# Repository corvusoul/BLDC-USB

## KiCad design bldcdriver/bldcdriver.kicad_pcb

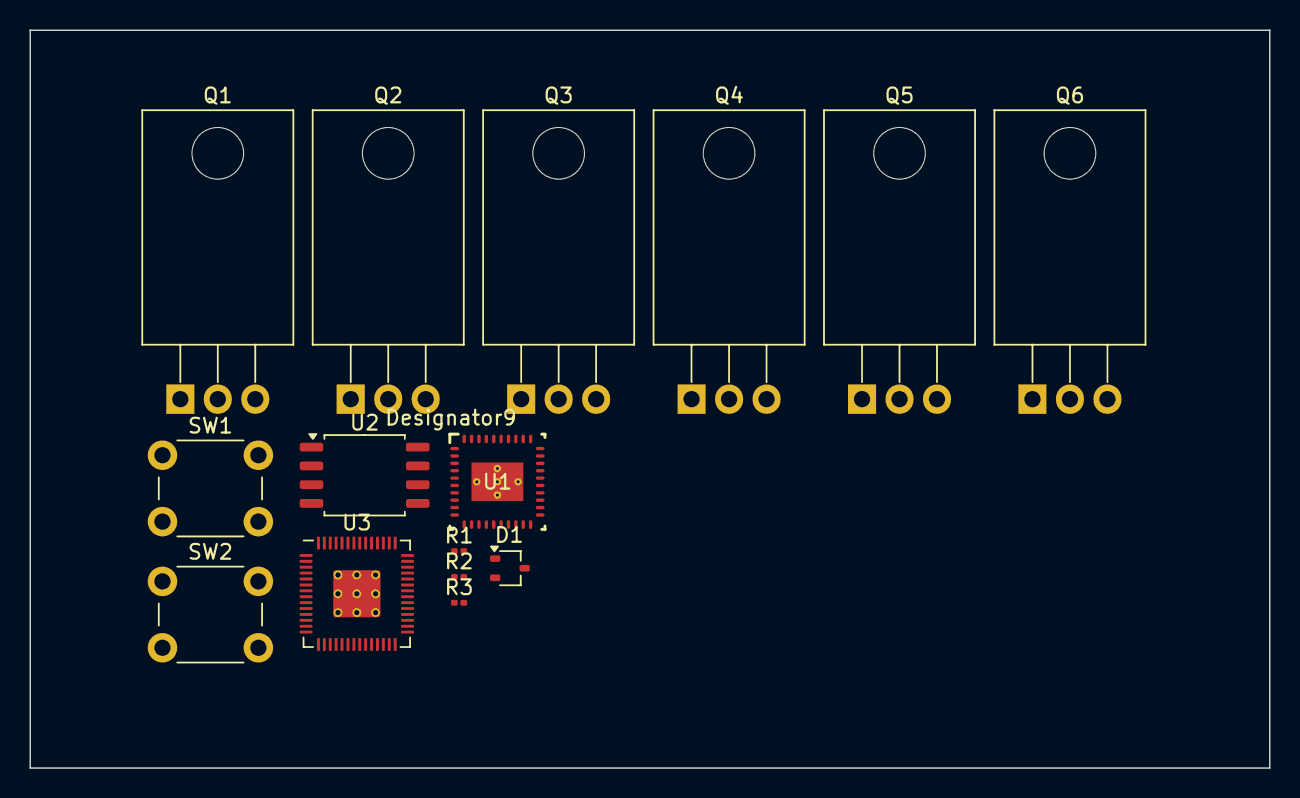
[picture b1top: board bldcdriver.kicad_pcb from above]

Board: 2 copper layers, 84.0 x 50.0 mm, 15 parts (0 on the bottom side), 35 nets, no tracks yet.

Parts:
D1: BAT54W; SOT-323_SC-70
Q1, Q2, Q3, Q4, Q5, Q6: IRF3205; TO-220-3_Horizontal_TabDown
R1, R2, R3: R; R_0201_0603Metric
SW1, SW2: SW_Push; SW_PUSH_6mm
U1: DRV8304SRHAR; RHA0040E
U2: W25Q128JVS; SOIC-8_5.23x5.23mm_P1.27mm
U3: RP2040; RP2040-QFN-56

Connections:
+1V1: U3.23 (DVDD), U3.45 (VREG_VOUT), U3.50 (DVDD)
+3.3V: U1.24 (VREF), U1.33 (DVDD), U2.8 (VCC), U3.1 (IOVDD), U3.10 (IOVDD), U3.22 (IOVDD), U3.33 (IOVDD), U3.42 (IOVDD), U3.43 (ADC_AVDD), U3.44 (VREG_IN), U3.48 (USB_VDD), U3.49 (IOVDD)
+24V: Q1.2 (D), Q3.2 (D), Q5.2 (D), U1.4 (VM), U1.5 (VDRAIN)
/DREN: U1.30 (ENABLE), U3.8 (GPIO6)
/GHA: Q1.1 (G), U1.6 (GHA)
/GHB: Q3.1 (G), U1.15 (GHB)
/GHC: Q5.1 (G), U1.16 (GHC)
/GLA: Q2.1 (G), U1.8 (GLA)
/GLB: Q4.1 (G), U1.13 (GLB)
/GLC: Q6.1 (G), U1.18 (GLC)
/INHA: U1.34 (INHA), U3.2 (GPIO0)
/INHB: U1.36 (INHB), U3.4 (GPIO2)
/INHC: U1.38 (INHC), U3.6 (GPIO4)
/INLA: U1.35 (INLA), U3.3 (GPIO1)
/INLB: U1.37 (INLB), U3.5 (GPIO3)
/INLC: U1.39 (INLC), U3.7 (GPIO5)
/Phase A: Q1.3 (S), Q2.2 (D), U1.7 (SHA)
/Phase B: Q3.3 (S), Q4.2 (D), U1.14 (SHB)
/Phase C: Q5.3 (S), Q6.2 (D), U1.17 (SHC)
/QSPI_SCLK: U2.6 (CLK), U3.52 (QSPI_SCLK)
/QSPI_SD0: U2.5 (DI(IO0)), U3.53 (QSPI_SD0)
/QSPI_SD1: U2.2 (DO(IO1)), U3.55 (QSPI_SD1)
/QSPI_SD2: U2.3 (IO2), U3.54 (QSPI_SD2)
/QSPI_SD3: U2.7 (IO3), U3.51 (QSPI_SD3)
/QSPI_SS: U2.1 (~CS), U3.56 (QSPI_SS)
/SPA: Q2.3 (S), R1.1, U1.9 (SPA)
/SPB: Q4.3 (S), R2.1, U1.12 (SPB)
/SPC: Q6.3 (S), R3.1, U1.19 (SPC)
/SPI_CLK: U1.28 (SCLK), U3.29 (GPIO18)
/SPI_CSn_DRV: U1.29 (SCS_N), U3.28 (GPIO17)
/SPI_SDI: U1.26 (SDO), U3.27 (GPIO16)
/SPI_SDO: U1.27 (SDI), U3.30 (GPIO19)
/nFAULT: U1.25 (FAULT_N), U3.9 (GPIO7)
GND: R1.2, R2.2, R3.2, SW1.2, SW2.1, U1.10 (SNA), U1.11 (SNB), U1.20 (SNC), U1.31 (CAL), U1.32 (AGND), U1.40 (PGND), U1.41 (PAD), U2.4 (GND), U3.19 (TESTEN), U3.57 (GND)
unnamed: SW2.2, U3.26 (RUN)

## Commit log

2024-08-10 Added DRV8304 footprint files and .gitignore
2024-08-10 Added a README.md
2024-08-11 Added Microcontroller (STM) and Gate Driver (DRV)
2024-08-22 Finished N MOSFET Triple Half Bridge Circuit with Global Labels, looking if I want to use a P MOSFET
2024-08-22 Few more connections and capacitors
2024-09-25 Few changes, not sure
2024-10-02 Replaced STM32 with RP2040
2024-11-01 Replaced the mistake in symbol from H to S, redid the connections, cleaned up local library folders, added proper net labels
2024-11-01 Created hierarchical sheets for every major component with a very basic block diagram on the front page
2024-11-02 Added the QSPI chip but not fully interfaced with the button/jumper, added decoupling capacitors for the RP2040
2024-11-02 Added a USB C Connector and wired it up to act as USB 2.0
2024-11-22 Finished DRV side fully, RP2040 almost fully done, FOC sensorless and sensor parts and power parts are left
2024-11-24 Increased main sheet size to A2 and fit everything there
